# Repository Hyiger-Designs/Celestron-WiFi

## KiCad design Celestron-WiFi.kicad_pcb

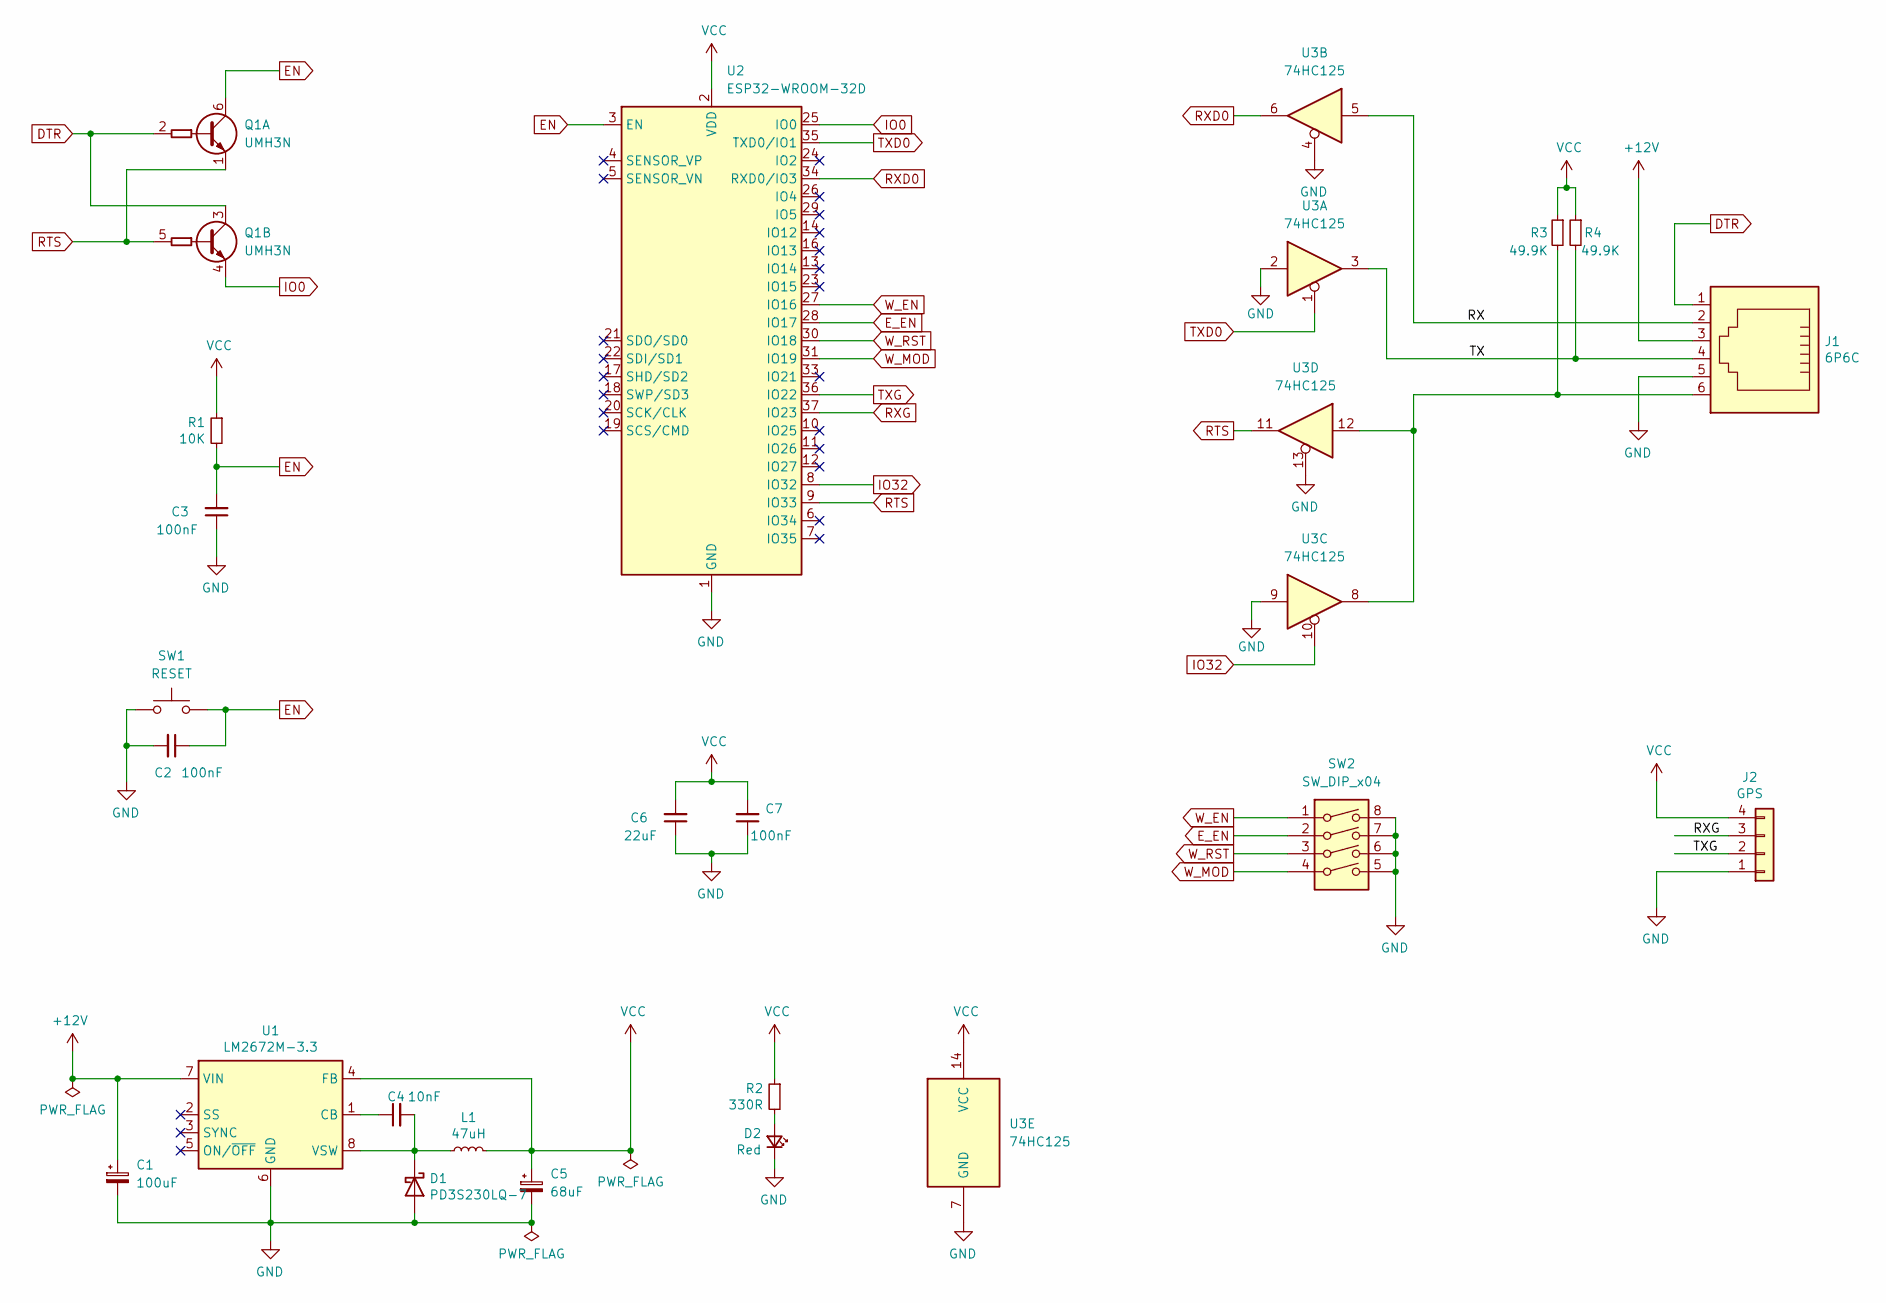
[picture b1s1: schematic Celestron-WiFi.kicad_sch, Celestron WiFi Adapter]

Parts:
C1: 100uF; CP_EIA-7343-43_Kemet-X
C2, C3, C7: 100nF; C_0603_1608Metric
C4: 10nF; C_0603_1608Metric
C5: 68uF; CP_EIA-3216-18_Kemet-A
C6: 22uF; C_0805_2012Metric; MPN C0805C226M8PACTU
D1: PD3S230LQ-7; D_PowerDI-323; MPN PD3S230LQ-7
D2: Red; LED_0603_1608Metric
J1: 6P6C; RJ12_Amphenol_54601; MPN 54601-906001WPLF
J2: GPS; JST_SH_BM04B-SRSS-TB_1x04-1MP_P1.00mm_Vertical
L1: 47uH; L_Coilcraft_LPS5030; MPN MSS6132-473MLC
Q1: UMH3N; SOT-363_SC-70-6
R1: 10K; R_0603_1608Metric; MPN CR0603-FX-1000ELF
R2: 330R; R_0603_1608Metric
R3, R4: 49.9K; R_0603_1608Metric; MPN CR0603-FX-4992ELF
SW1: RESET; SW_Push_SPST_NO_Alps_SKRK
SW2: SW_DIP_x04; SW_DIP_SPSTx04_Slide_6.7x11.72mm_W8.61mm_P2.54mm_LowProfile; MPN 219-4MS
U1: LM2672M-3.3; SOIC-8_3.9x4.9mm_P1.27mm; MPN LM2672M-3.3/NOPB
U2: ESP32-WROOM-32D; ESP32-WROOM-32
U3: 74HC125; TSSOP-14_4.4x5mm_P0.65mm

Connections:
+12V: C1.1, J1.3, U1.7 (VIN)
/RX: J1.2, U3.5
/TX: J1.4, R4.2, U3.3
DTR: J1.1, Q1.2 (B1), Q1.3 (C2)
EN: C2.1, C3.2, Q1.6 (C1), R1.2, SW1.2, U2.3 (EN)
E_EN: SW2.2, U2.28 (IO17)
GND: C1.2, C2.2, C3.1, C5.2, C6.1, C7.1, D1.2 (A), D2.1 (K), J1.5, J2.1, SW1.1, SW2.5, SW2.6, SW2.7, SW2.8, U1.6 (GND), U2.1 (GND), U2.15 (GND), U2.38 (GND), U2.39 (GND), U3.2, U3.4, U3.7 (GND), U3.9, U3.13
IO0: Q1.4 (E2), U2.25 (IO0)
IO32: U2.8 (IO32), U3.10
unnamed: C4.1, U1.1 (CB)
unnamed: C4.2, D1.1 (K), L1.1, U1.8 (VSW)
unnamed: D2.2 (A), R2.2
unnamed: J1.6, R3.2, U3.8, U3.12
RTS: Q1.1 (E1), Q1.5 (B2), U2.9 (IO33), U3.11
RXD0: U2.34 (RXD0/IO3), U3.6
RXG: J2.3, U2.37 (IO23)
TXD0: U2.35 (TXD0/IO1), U3.1
TXG: J2.2, U2.36 (IO22)
VCC: C5.1, C6.2, C7.2, J2.4, L1.2, R1.1, R2.1, R3.1, R4.1, U1.4 (FB), U2.2 (VDD), U3.14 (VCC)
W_EN: SW2.1, U2.27 (IO16)
W_MOD: SW2.4, U2.31 (IO19)
W_RST: SW2.3, U2.30 (IO18)

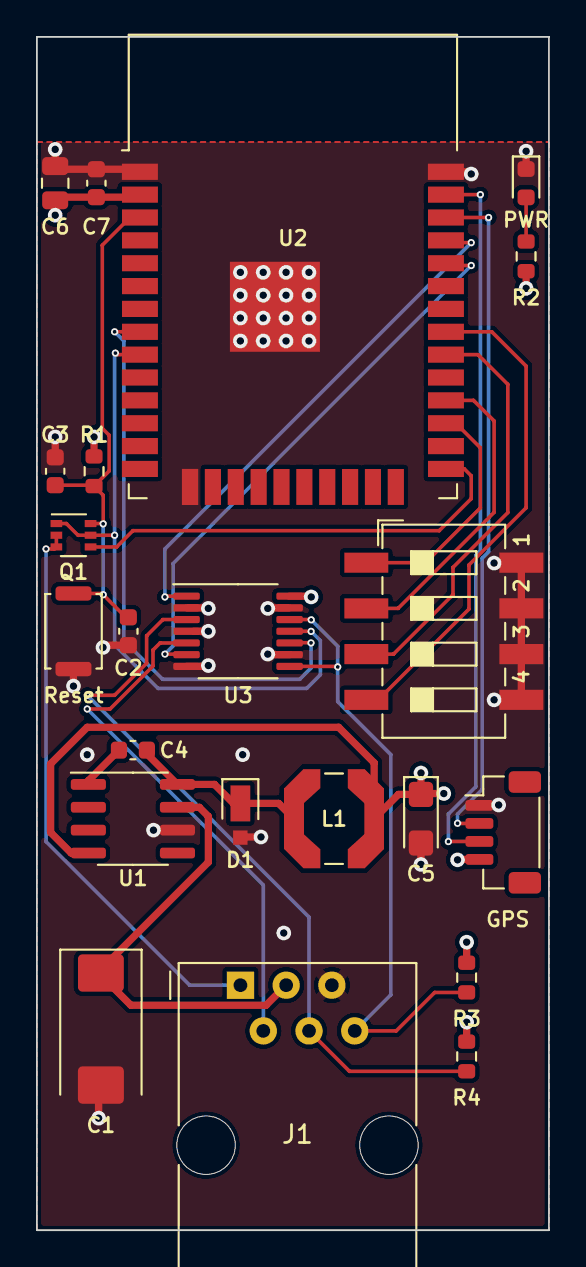
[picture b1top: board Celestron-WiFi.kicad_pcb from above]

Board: 4 copper layers, 28.4 x 66.3 mm, 22 parts (0 on the bottom side), 22 nets.

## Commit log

2021-12-09 Initial Revision
2021-12-18 routing changes
2021-12-18 removed gerbers
2021-12-25 schematic fixes
